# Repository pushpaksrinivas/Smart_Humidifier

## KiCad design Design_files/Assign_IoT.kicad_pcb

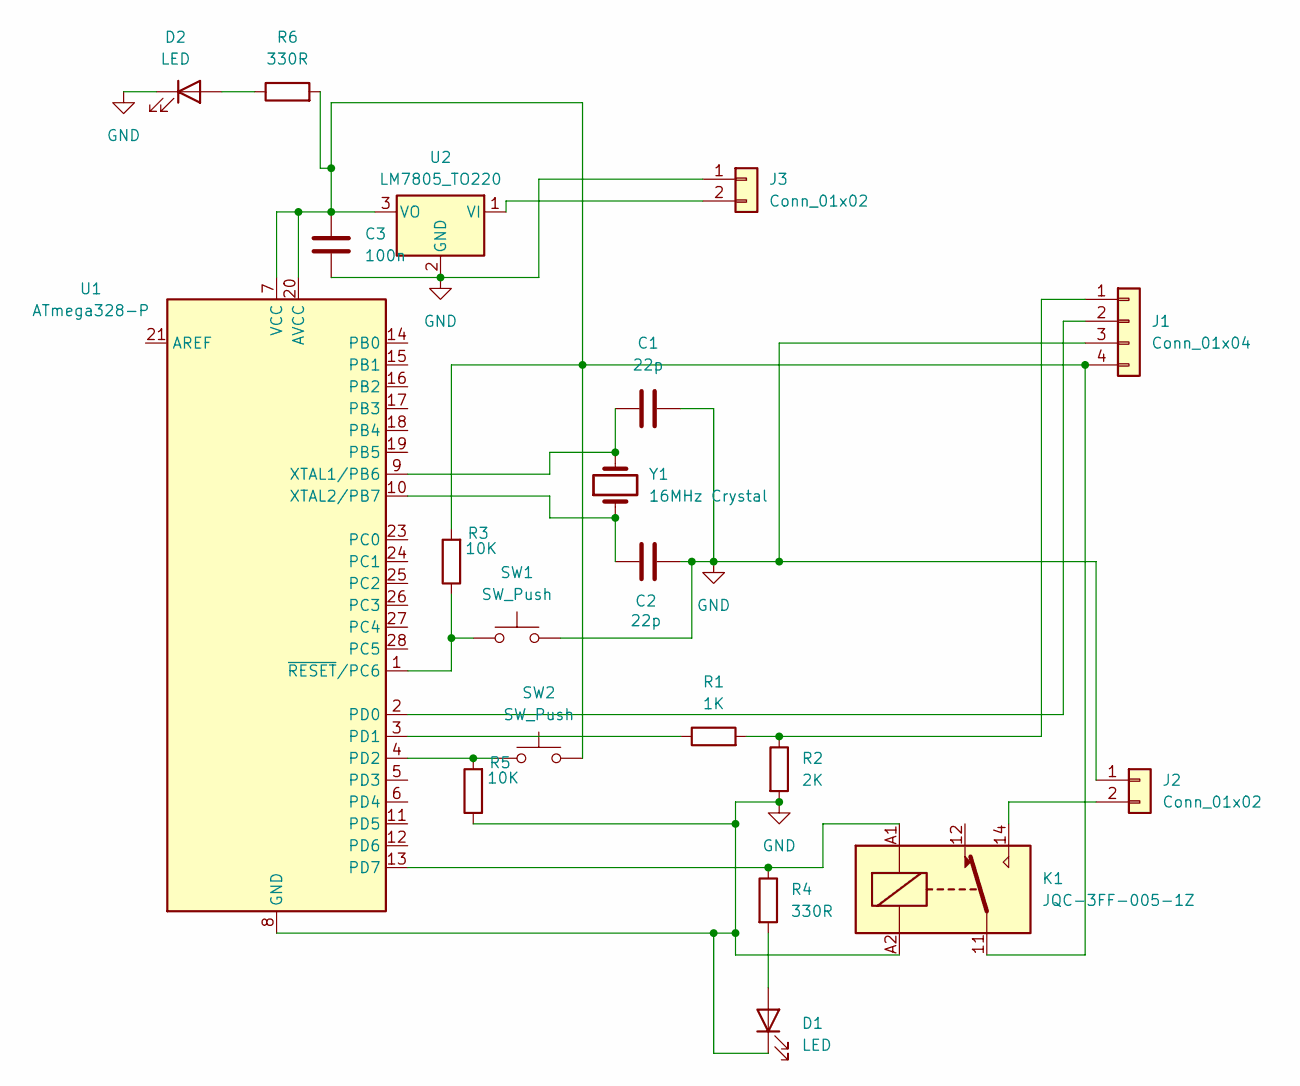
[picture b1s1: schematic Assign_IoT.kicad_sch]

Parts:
C1, C2: 22p; C_0805_2012Metric_Pad1.18x1.45mm_HandSolder
C3: 100n; C_0805_2012Metric_Pad1.18x1.45mm_HandSolder
D1, D2: LED; LED_D5.0mm
J1: Conn_01x04; PinHeader_1x04_P2.54mm_Vertical
J2, J3: Conn_01x02; PinHeader_1x02_P2.54mm_Vertical
K1: JQC-3FF-005-1Z; Relay_SPDT_Hongfa_JQC-3FF_0XX-1Z
R1: 1K; R_1206_3216Metric_Pad1.30x1.75mm_HandSolder
R2: 2K; R_1206_3216Metric_Pad1.30x1.75mm_HandSolder
R3, R5: 10K; R_1206_3216Metric_Pad1.30x1.75mm_HandSolder
R4, R6: 330R; R_1206_3216Metric_Pad1.30x1.75mm_HandSolder
SW1, SW2: SW_Push; SW_PUSH_6mm
U1: ATmega328-P; DIP-28_W7.62mm
U2: LM7805_TO220; SOT-223
Y1: 16MHz Crystal; Crystal_HC49-4H_Vertical

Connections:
GND: C1.2, C2.1, C3.1, D1.1 (K), D2.1 (K), J1.3, J2.1, J3.1, K1.A2, R2.2, R5.1, SW1.2, U1.8 (GND), U1.22 (GND), U2.2 (GND)
unnamed: D1.2 (A), R4.2
unnamed: D2.2 (A), R6.1
unnamed: J1.1, R1.2, R2.1
unnamed: J1.2, U1.2 (PD0)
unnamed: C3.2, J1.4, K1.11, R3.2, R6.2, SW2.2, U1.7 (VCC), U1.20 (AVCC), U2.3 (VO)
unnamed: J2.2, K1.14
unnamed: J3.2, U2.1 (VI)
unnamed: R1.1, U1.3 (PD1)
unnamed: R5.2, SW2.1, U1.4 (PD2)
unnamed: K1.A1, R4.1, U1.13 (PD7)
unnamed: C1.1, U1.9 (XTAL1/PB6), Y1.2
unnamed: C2.2, U1.10 (XTAL2/PB7), Y1.1
unnamed: R3.1, SW1.1, U1.1 (~RESET/PC6)

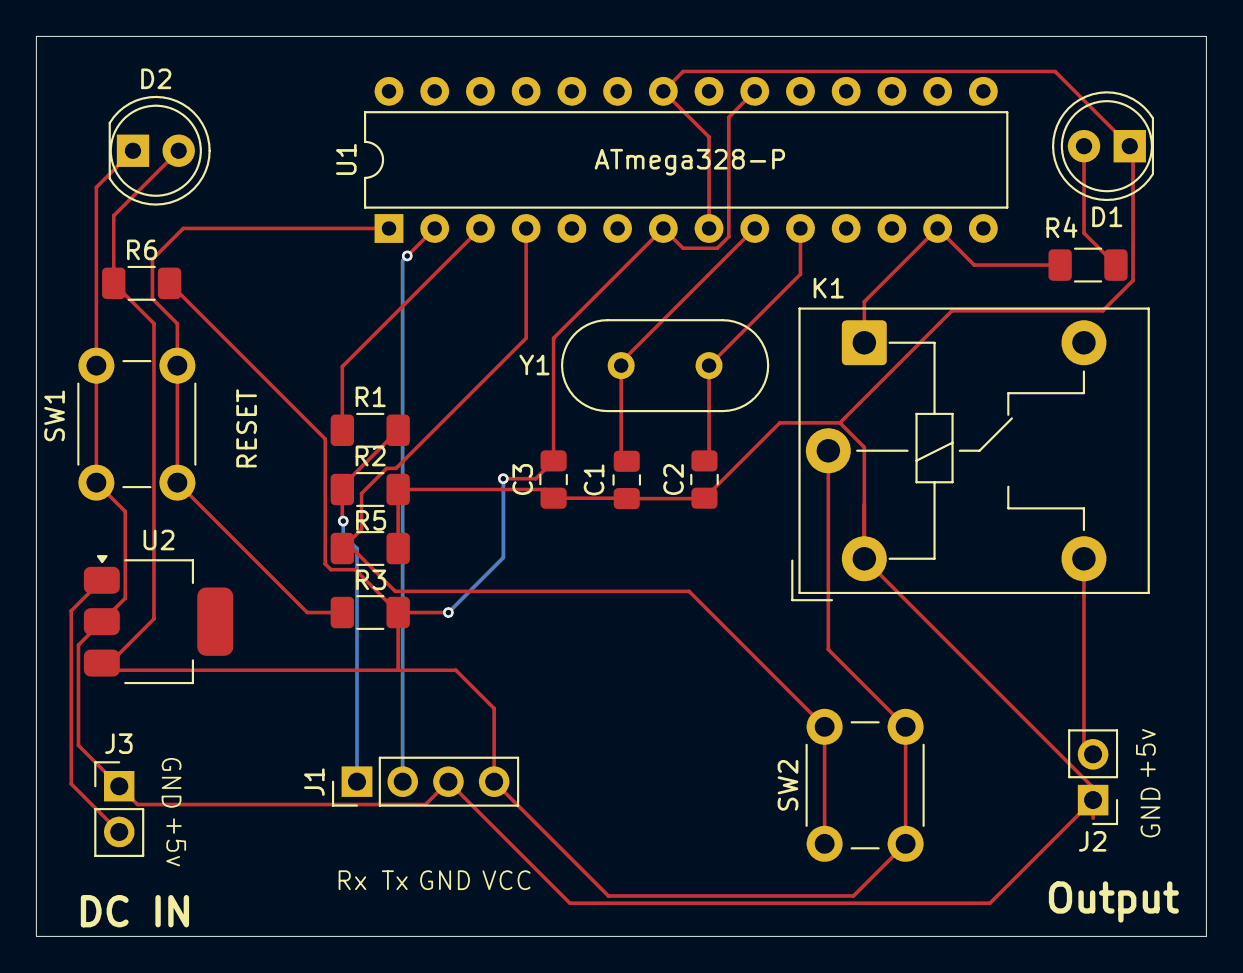
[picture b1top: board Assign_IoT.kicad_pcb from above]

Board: 2 copper layers, 65.0 x 50.0 mm, 20 parts (0 on the bottom side), 14 nets.

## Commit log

2025-05-24 Create temp
